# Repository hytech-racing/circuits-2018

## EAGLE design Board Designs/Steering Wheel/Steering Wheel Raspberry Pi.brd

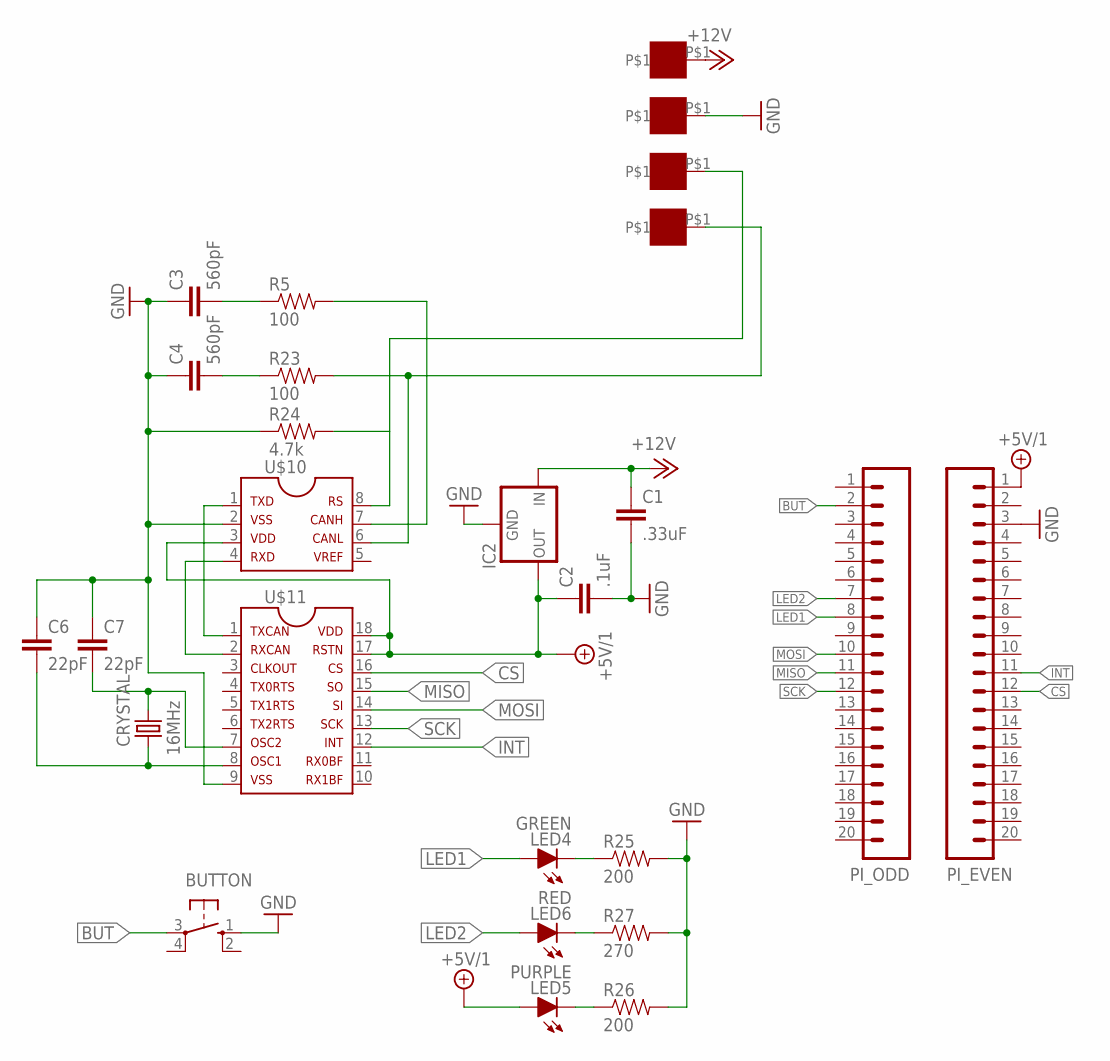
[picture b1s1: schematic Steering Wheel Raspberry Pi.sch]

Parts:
BUTTON: BTN_10-XX; B3F-10XX
C1: .33uF; 0805
C2: .1uF; 0805
C3, C4: 560pF; 0805
C6, C7: 22pF; 0805
CRYSTAL: 16MHz; HC49UP
IC2: OKI-78SR-5/1.5-W36-C_VERT; TO-220
LED4: GREEN; LED-805
LED5: PURPLE; LED-805
LED6: RED; LED-805
PI_EVEN: M20; 1X20
PI_ODD: M20; 1X20
R5, R23: 100; 0805
R24: 4.7k; 0805
R25, R26: 200; 0805
R27: 270; 0805
U$1, U$2, U$3, U$4: SOLDER_PAD; SOLDER_PAD_XSMALL
U$10: MCP2551; SOIC-08
U$11: MCP2515SMD; SOIC-18W

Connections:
+5V/1: C2.1, IC2.3 (OUT), LED5.A, PI_EVEN.1, U$10.3, U$11.17, U$11.18
+12V: C1.1, IC2.1 (IN), U$1.P$1
BUT: BUTTON.3, PI_ODD.2
CAN-H: R5.2, U$10.7
CAN-L: R23.2, U$4.P$1, U$10.6
CS: PI_EVEN.12, U$11.16
GND: BUTTON.1 (S), C1.2, C2.2, C3.1, C4.1, C6.1, C7.1, IC2.2 (GND), PI_EVEN.3, R24.1, R25.2, R26.2, R27.2, U$2.P$1, U$10.2, U$11.9
INT: PI_EVEN.11, U$11.12
LED1: LED4.A, PI_ODD.8
LED2: LED6.A, PI_ODD.7
MISO: PI_ODD.11, U$11.15
MOSI: PI_ODD.10, U$11.14
unnamed: U$10.1, U$11.1
unnamed: U$10.4, U$11.2
unnamed: C6.2, CRYSTAL.2, U$11.8
unnamed: R24.2, U$3.P$1, U$10.8
unnamed: C7.2, CRYSTAL.1, U$11.7
unnamed: C3.2, R5.1
unnamed: C4.2, R23.1
unnamed: LED4.C, R25.1
unnamed: LED5.C, R26.1
unnamed: LED6.C, R27.1
SCK: PI_ODD.12, U$11.13

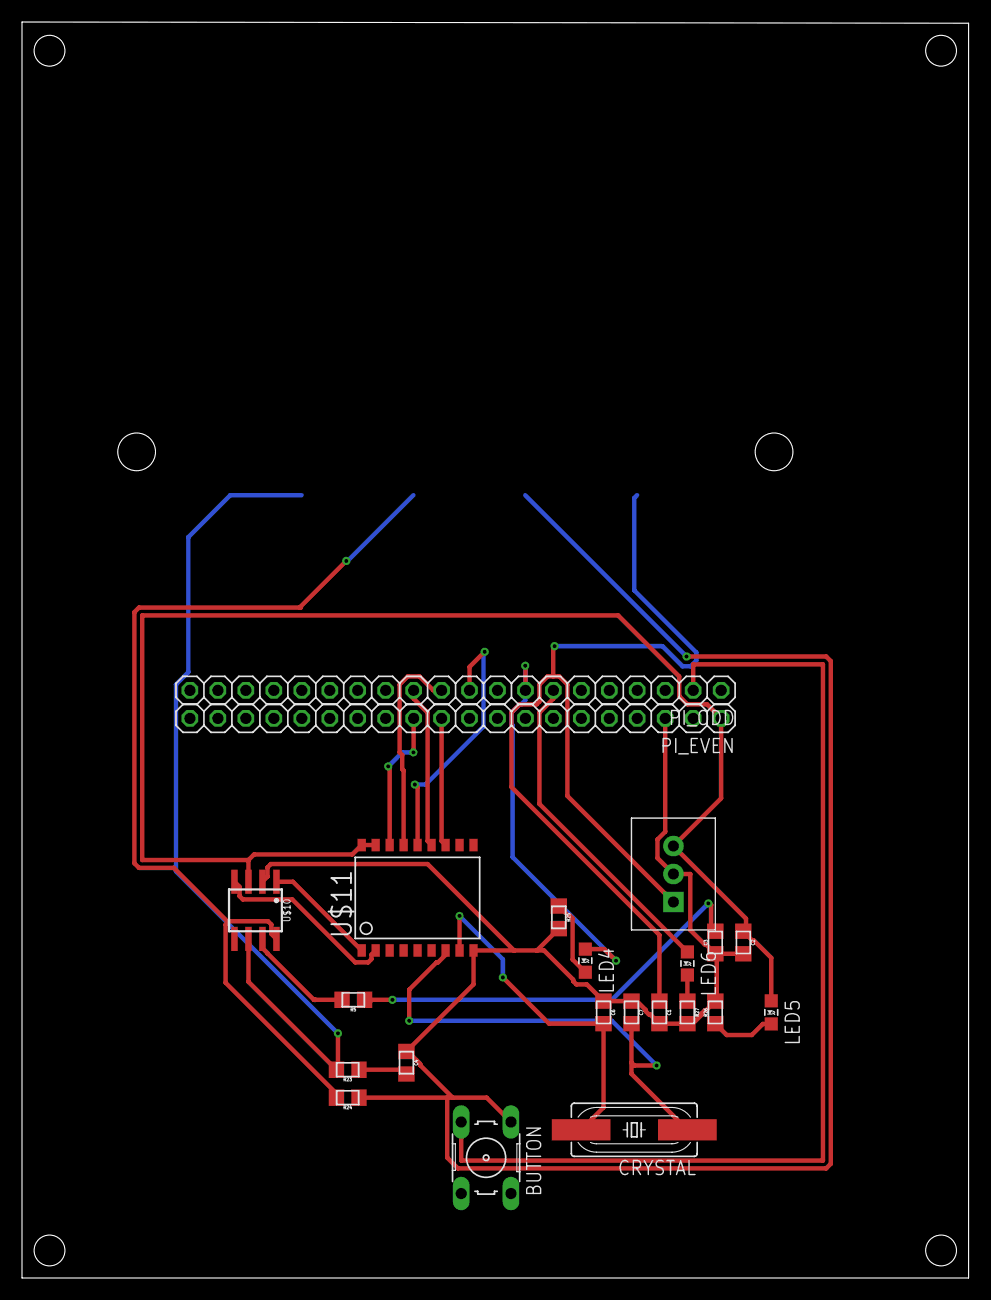
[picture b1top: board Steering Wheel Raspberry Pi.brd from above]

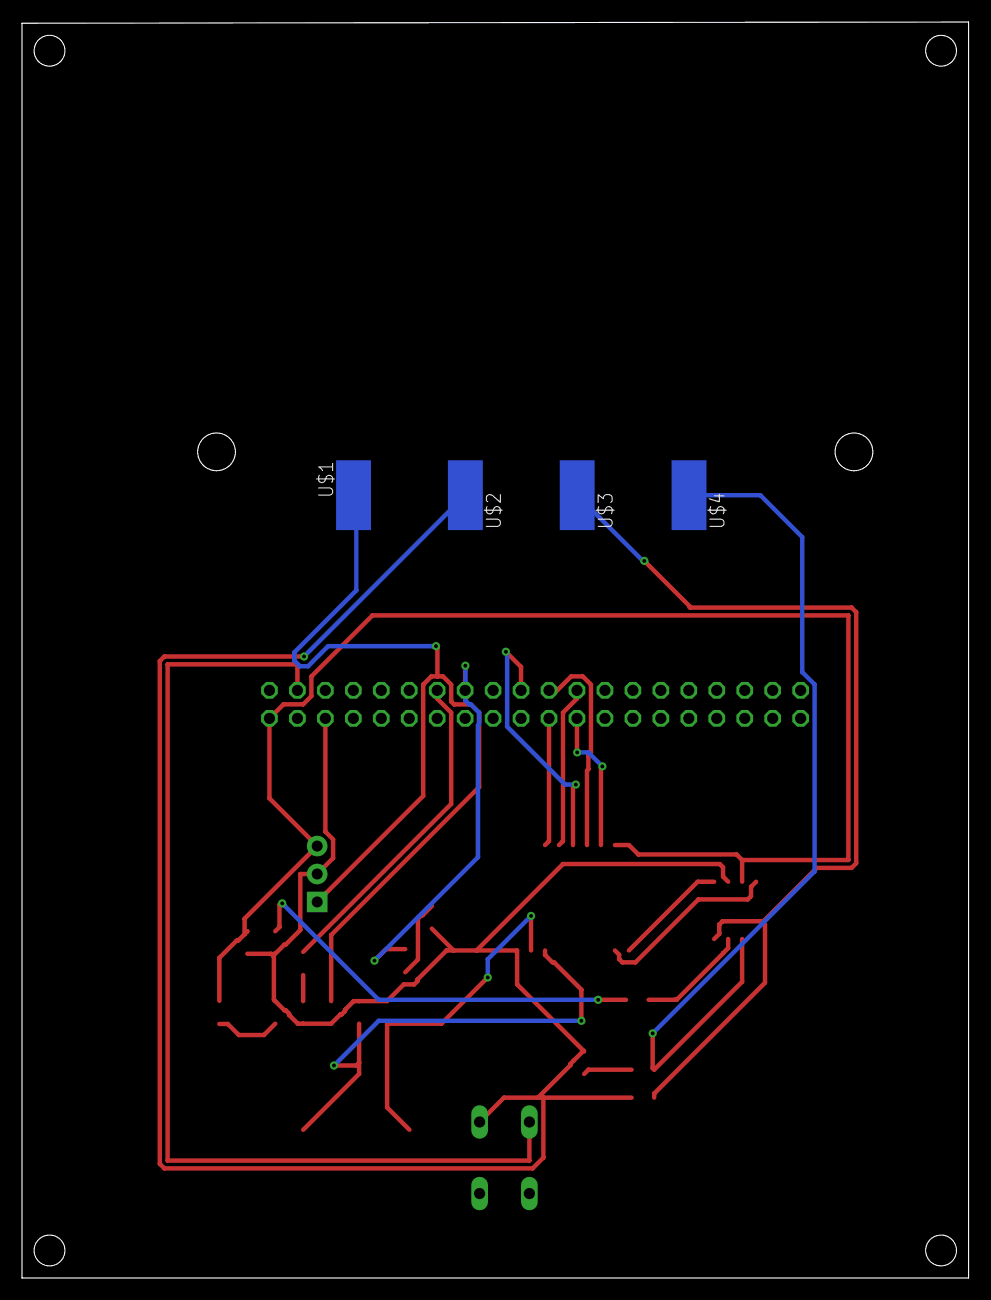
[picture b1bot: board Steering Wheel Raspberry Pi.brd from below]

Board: 2 copper layers, 86.0 x 114.1 mm, 26 parts (4 on the bottom side), 23 nets.

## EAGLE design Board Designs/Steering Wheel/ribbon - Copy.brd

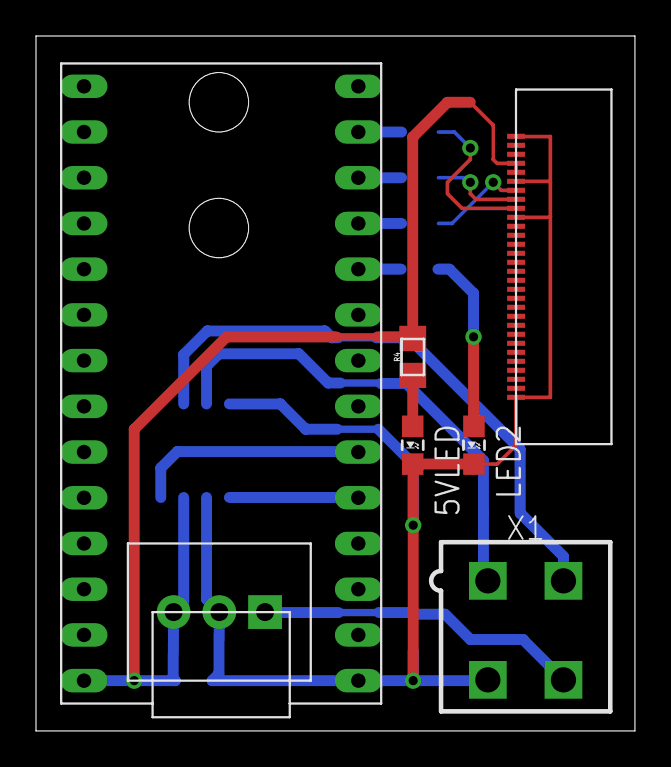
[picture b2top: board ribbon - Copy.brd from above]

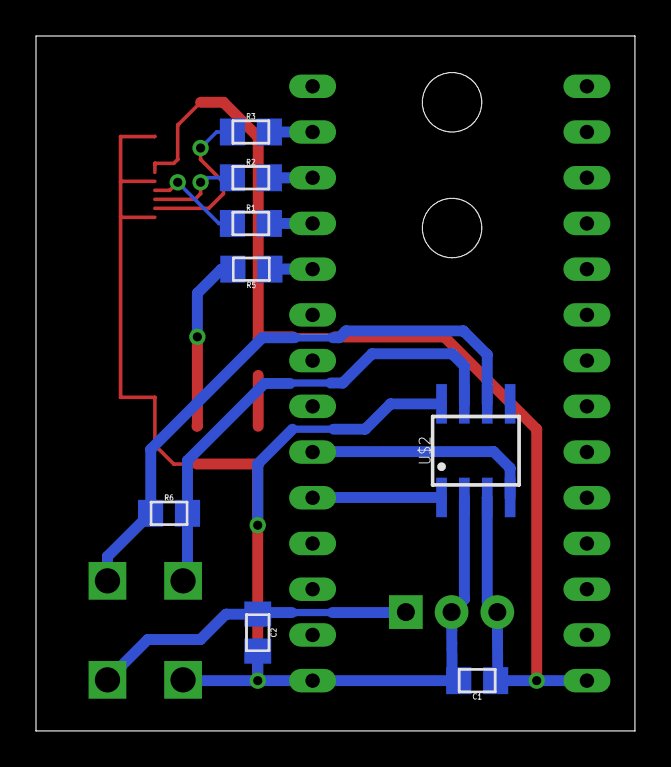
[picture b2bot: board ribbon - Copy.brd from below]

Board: 2 copper layers, 33.3 x 38.6 mm, 15 parts (8 on the bottom side), 16 nets.

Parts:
5VLED: LED-805
C1, C2: 0805
IC1: TO-220
LED2: LED-805
R1, R2, R3: 68; 0805
R4, R5: 450; 0805
R6: 120; 0805
U$1: TEENSY_3.2_SIMPLE
U$2: MCP2551; SOIC-08
U$3: FFC-30P-0.5MM
X1: CONNECTOR-4; MINIFIT_5566-4

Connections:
+5V: C1.1, IC1.3, R4.2, U$1.VIN, U$2.3, U$3.26, U$3.27
+12V: C2.1, IC1.1, X1.4
CANH: R6.2, U$2.7, X1.1
CANL: R6.1, U$2.6, X1.2
CANRX: U$1.D4(CANRX), U$2.4
CANTX: U$1.D3(CANTX), U$2.1
DISP_RX: R2.1, U$3.23
DISP_TX: R1.1, U$3.24
GND: 5VLED.C, C1.2, C2.2, IC1.2, LED2.C, U$1.GND, U$2.2, U$2.8, U$3.1, U$3.21, U$3.25, U$3.30, X1.3
unnamed: R1.2, U$1.D9(RX2)
unnamed: R2.2, U$1.D10(TX2)
unnamed: R3.2, U$1.D11
unnamed: 5VLED.A, R4.1
unnamed: LED2.A, R5.2
unnamed: R5.1, U$1.D8(TX3)
RESET: R3.1, U$3.22

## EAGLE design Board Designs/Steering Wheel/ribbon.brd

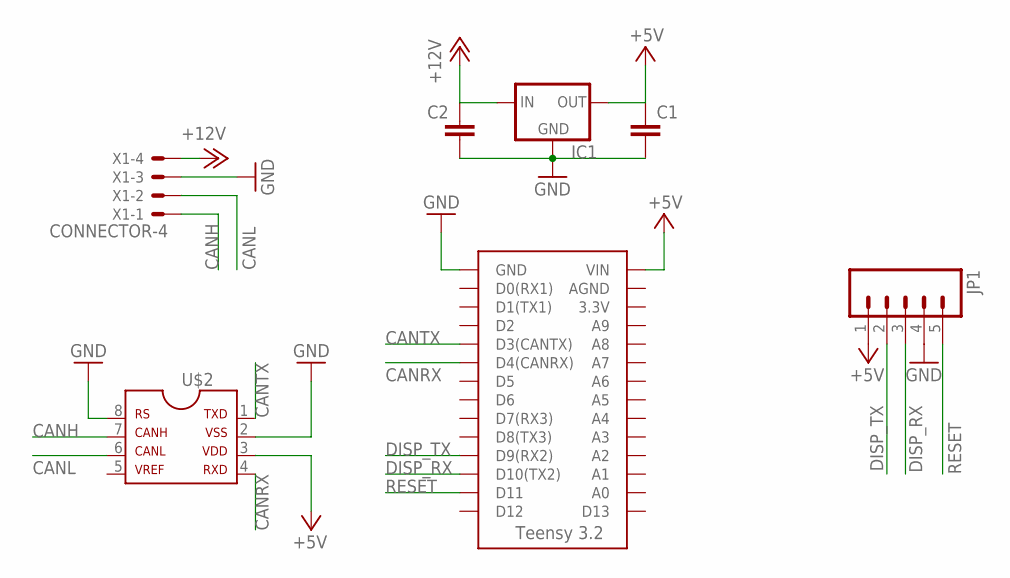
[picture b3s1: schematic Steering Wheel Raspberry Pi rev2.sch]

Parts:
C1, C2: CAP0805; 0805
IC1: 5VREG_L7805_VERT; TO-220
JP1: M05; 1X05
U$1: TEENSY_3.2_SIMPLE
U$2: MCP2551; SOIC-08
X1: CONNECTOR-4; MINIFIT_5566-4

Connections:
+5V: C1.1, IC1.3 (OUT), JP1.1, U$1.VIN, U$2.3
+12V: C2.1, IC1.1 (IN), X1.4
CANH: U$2.7, X1.1
CANL: U$2.6, X1.2
CANRX: U$1.D4(CANRX), U$2.4
CANTX: U$1.D3(CANTX), U$2.1
DISP_RX: JP1.3, U$1.D10(TX2)
DISP_TX: JP1.2, U$1.D9(RX2)
GND: C1.2, C2.2, IC1.2 (GND), JP1.4, U$1.GND, U$2.2, U$2.8, X1.3
RESET: JP1.5, U$1.D11

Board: 2 copper layers, 7 parts (0 on the bottom side), 10 nets, no tracks yet.

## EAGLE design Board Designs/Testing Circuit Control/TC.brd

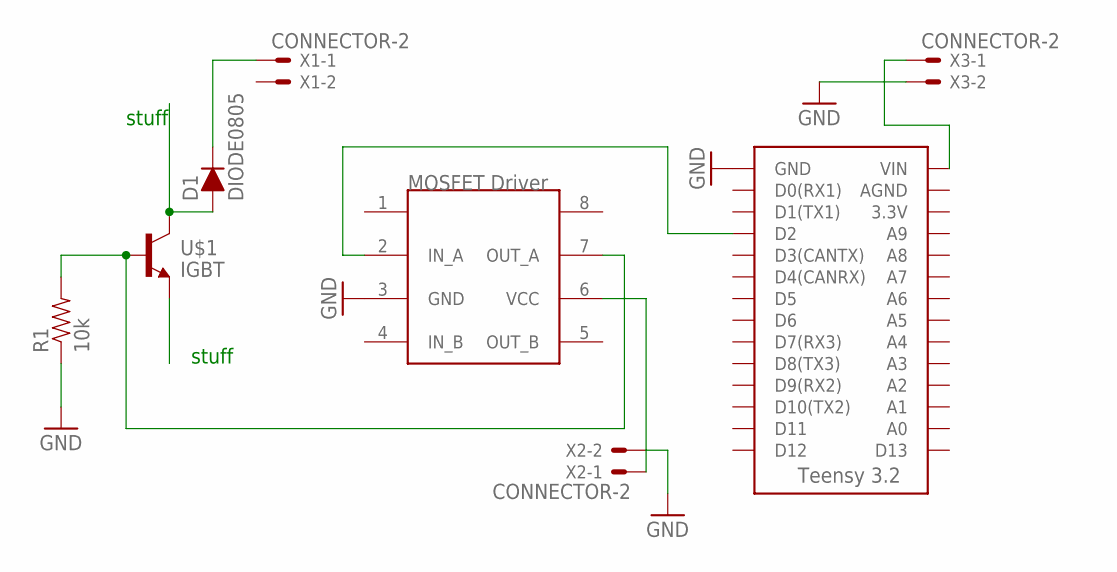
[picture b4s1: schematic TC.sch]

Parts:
D1: DIODE0805; 0805_D
R1: 10k; 0402-RES
U$1: IGBT
U$2: MC34152; SOIC-08
U$3: TEENSY_3.2_SIMPLE
X1, X2, X3: CONNECTOR-2; MINIFIT_5566-2

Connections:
GND: R1.1, U$2.3 (GND), U$3.GND, X2.2, X3.2
unnamed: D1.C, X1.1
unnamed: D1.A, U$1.P$2 (COLLECTOR)
unnamed: R1.2, U$1.P$3 (BASE), U$2.7 (OUT_A)
unnamed: U$2.2 (IN_A), U$3.D2
unnamed: U$1.P$1 (EMITTER), U$1.P$4 (EMITTER)
unnamed: U$2.6 (VCC), X2.1
unnamed: U$3.VIN, X3.1

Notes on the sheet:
stuff

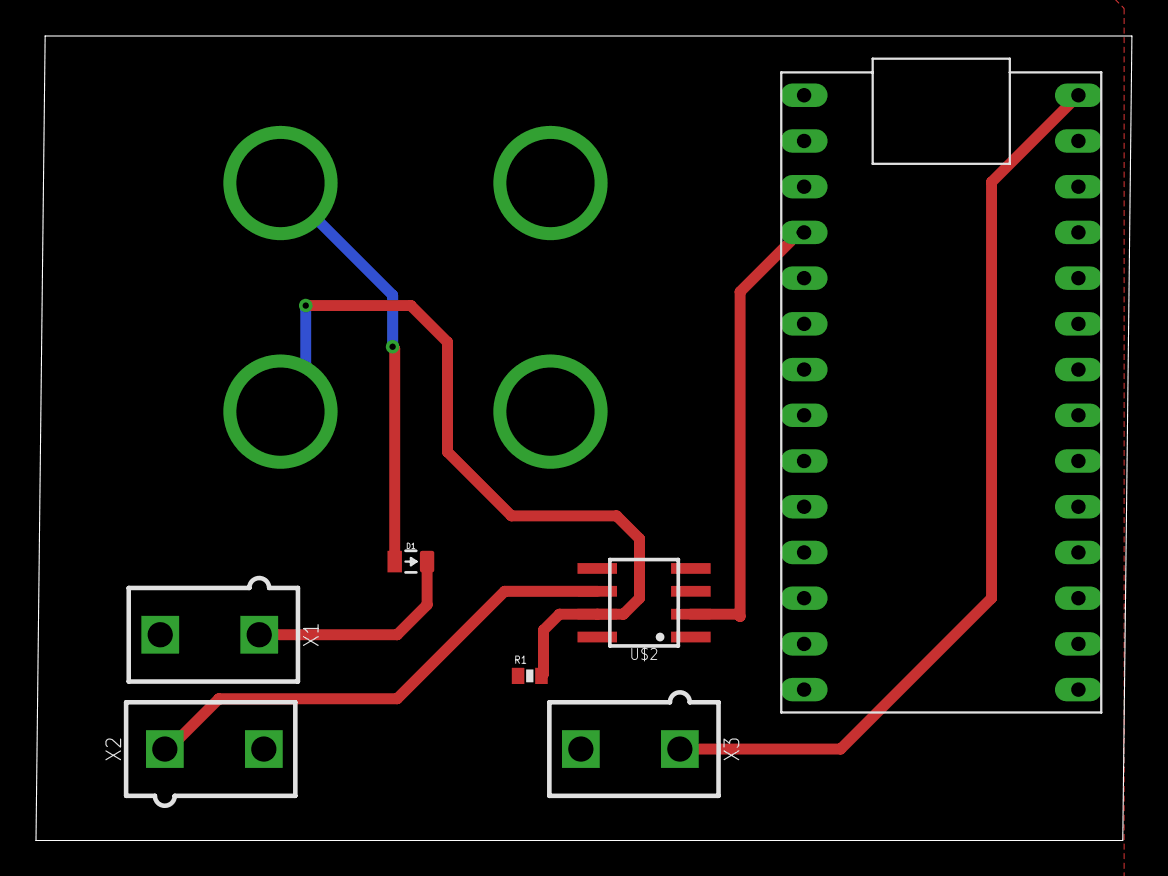
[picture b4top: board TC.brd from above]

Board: 2 copper layers, 60.9 x 44.7 mm, 8 parts (1 on the bottom side), 8 nets.

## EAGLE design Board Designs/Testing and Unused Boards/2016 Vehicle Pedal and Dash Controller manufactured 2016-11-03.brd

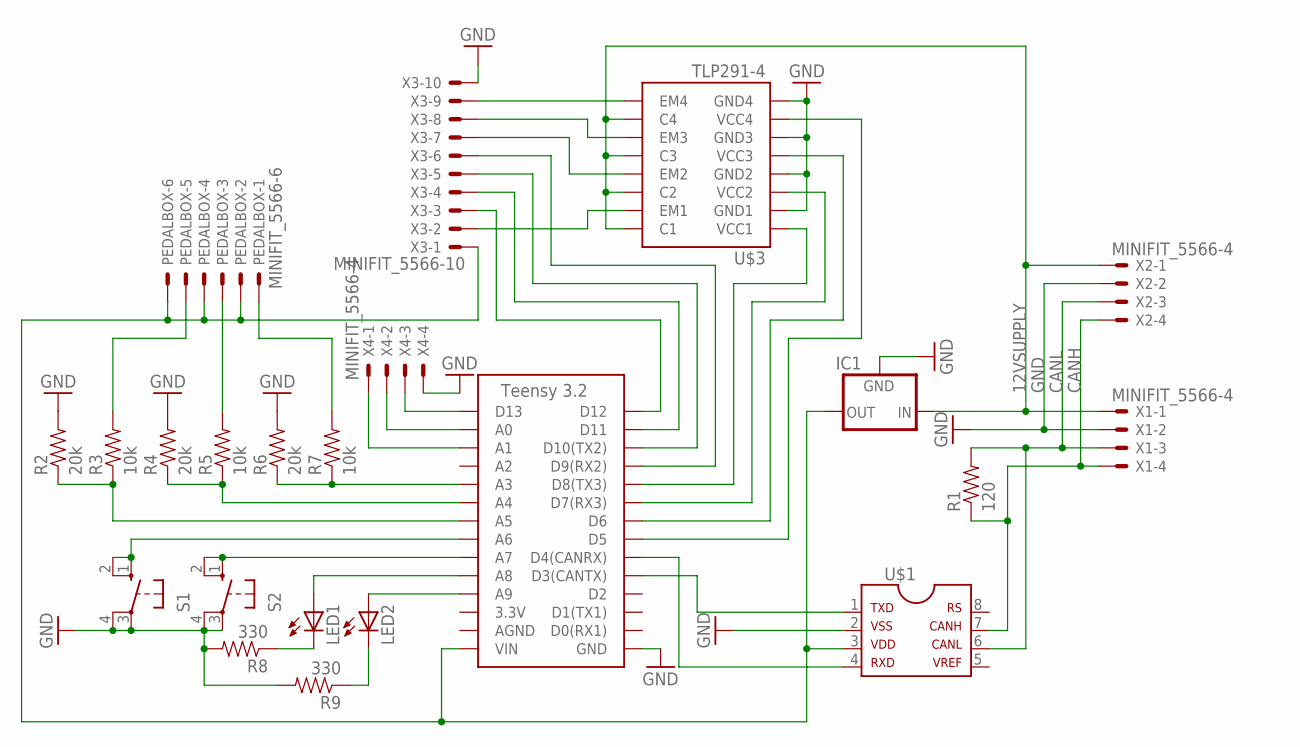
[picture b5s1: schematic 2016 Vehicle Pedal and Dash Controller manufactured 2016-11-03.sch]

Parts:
IC1: 5V_REGULATOR_LM340-NLM340MPX-5.0/NOPB; SOT223
LED1, LED2: LED-0805; LED-805
PEDALBOX: MINIFIT_5566-6
R1: 120; 0805
R2, R4, R6: 20k; 0805
R3, R5, R7: 10k; 0805
R8, R9: 330; 0805
S1, S2: BTN_10-XX; B3F-10XX
U$1: MCP2551; SOIC-08
U$2: TEENSY_3.2_SIMPLE
U$3: TLP291-4; SOIC-16
X1, X2, X4: MINIFIT_5566-4
X3: MINIFIT_5566-10

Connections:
12VSUPPLY: IC1.1 (IN), U$3.10 (C4), U$3.12 (C3), U$3.14 (C2), U$3.16 (C1), X1.1, X2.1
CANH: R1.1, U$1.7, X1.4, X2.4
CANL: R1.2, U$1.6, X1.3, X2.3
GND: IC1.2 (GND), IC1.4 (GND), R2.2, R4.2, R6.2, R8.2, R9.2, S1.3, S1.4 (P1), S2.3, S2.4 (P1), U$1.2, U$2.GND, U$3.2 (GND1), U$3.4 (GND2), U$3.6 (GND3), U$3.8 (GND4), X1.2, X2.2, X3.10, X4.4
unnamed: U$2.D12, X3.3
unnamed: IC1.3 (OUT), PEDALBOX.2, PEDALBOX.4, PEDALBOX.6, U$1.3, U$2.VIN, X3.1
unnamed: PEDALBOX.5, R3.2
unnamed: PEDALBOX.3, R5.2
unnamed: U$1.1, U$2.D3(CANTX)
unnamed: U$1.4, U$2.D4(CANRX)
unnamed: PEDALBOX.1, R7.2
unnamed: R2.1, R3.1, U$2.A5
unnamed: R4.1, R5.1, U$2.A4
unnamed: R6.1, R7.1, U$2.A3
unnamed: U$2.D11, X3.4
unnamed: U$2.D10(TX2), X3.5
unnamed: U$2.D9(RX2), X3.6
unnamed: U$2.D8(TX3), U$3.1 (VCC1)
unnamed: U$3.9 (EM4), X3.9
unnamed: U$3.11 (EM3), X3.8
unnamed: U$3.13 (EM2), X3.7
unnamed: U$3.15 (EM1), X3.2
unnamed: U$2.D7(RX3), U$3.3 (VCC2)
unnamed: U$2.D6, U$3.5 (VCC3)
unnamed: U$2.D5, U$3.7 (VCC4)
unnamed: S1.1 (S), S1.2 (S1), U$2.A6
unnamed: S2.1 (S), S2.2 (S1), U$2.A7
unnamed: LED1.A, U$2.A8
unnamed: LED2.A, U$2.A9
unnamed: LED1.C, R8.1
unnamed: LED2.C, R9.1
unnamed: U$2.D13, X4.3
unnamed: U$2.A0, X4.2
unnamed: U$2.A1, X4.1

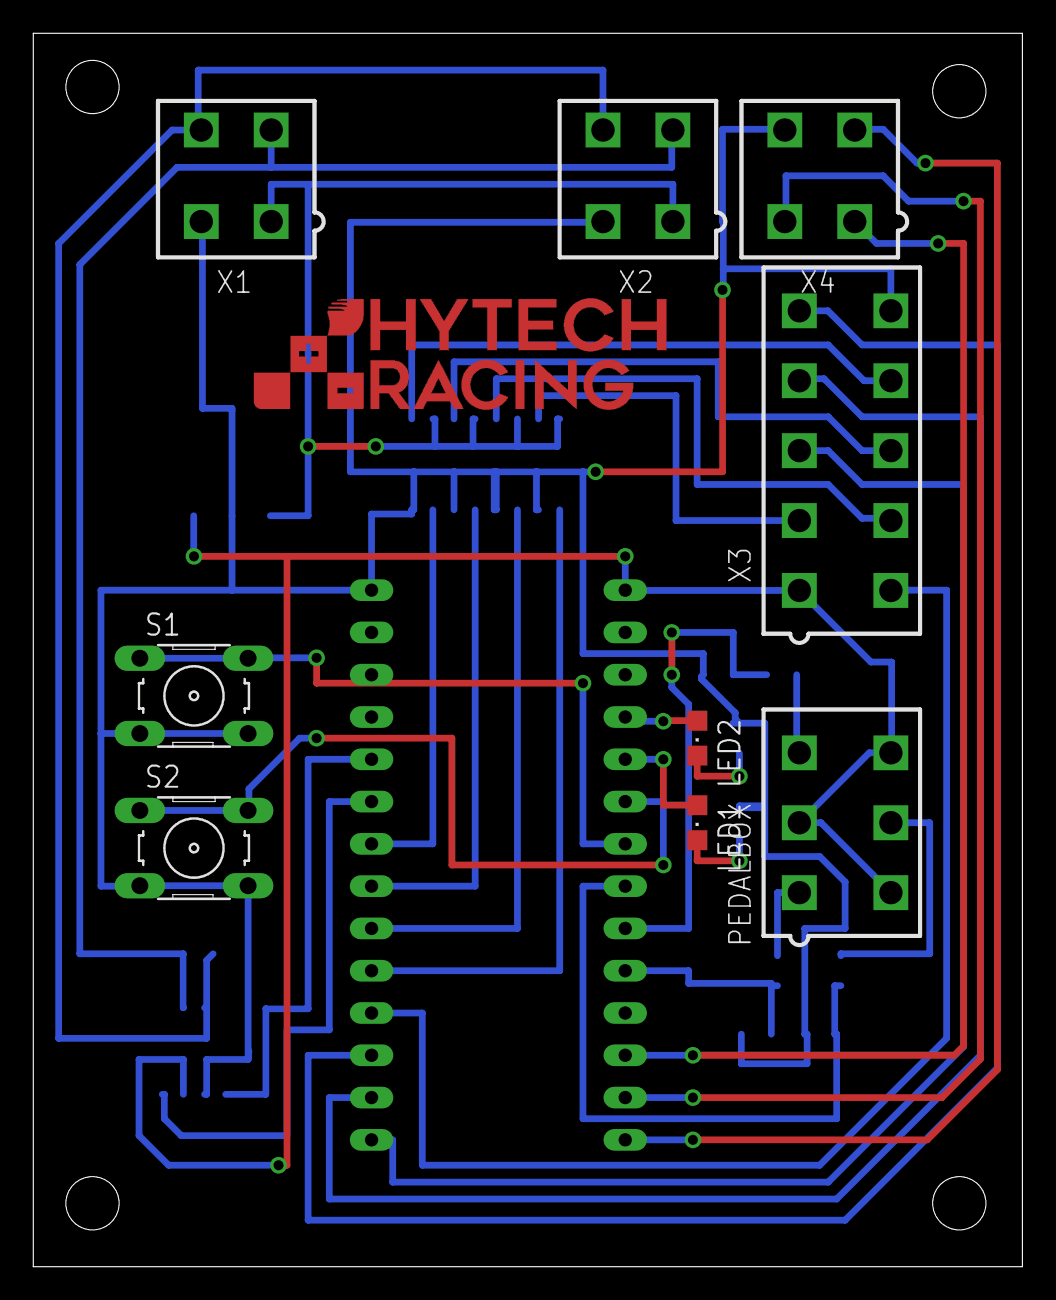
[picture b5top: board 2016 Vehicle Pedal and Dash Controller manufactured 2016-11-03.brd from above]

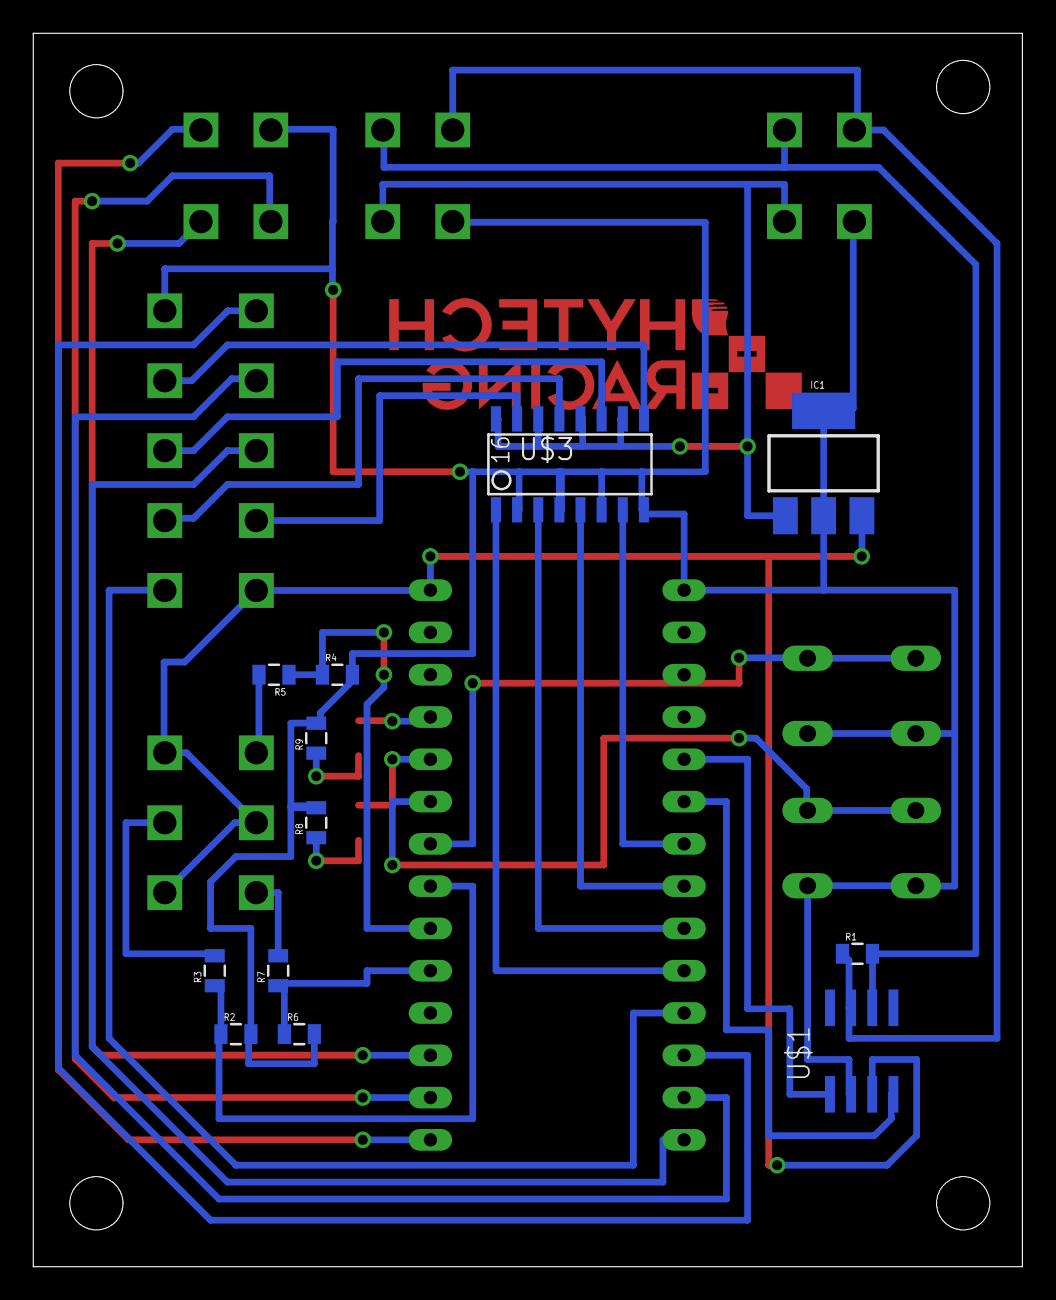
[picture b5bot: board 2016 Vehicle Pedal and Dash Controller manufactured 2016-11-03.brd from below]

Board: 2 copper layers, 59.4 x 74.1 mm, 22 parts (12 on the bottom side), 34 nets.

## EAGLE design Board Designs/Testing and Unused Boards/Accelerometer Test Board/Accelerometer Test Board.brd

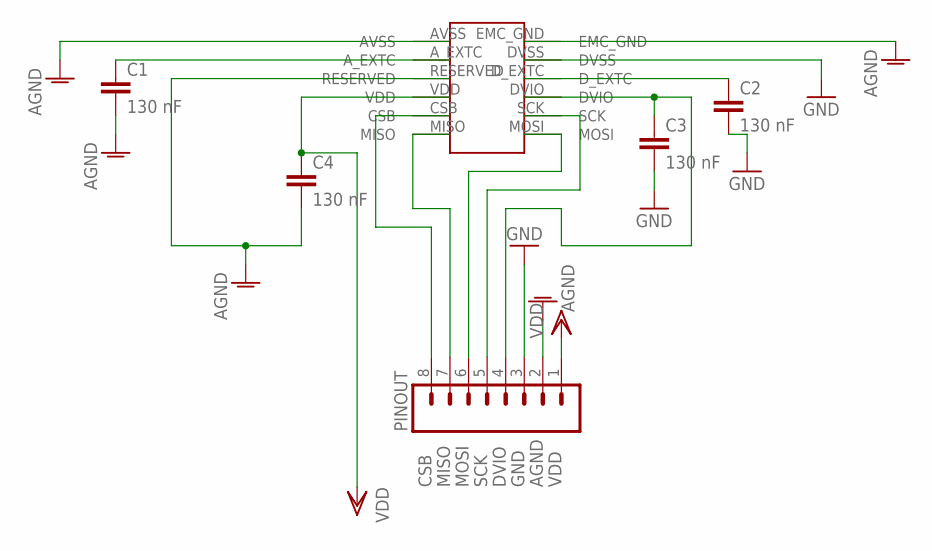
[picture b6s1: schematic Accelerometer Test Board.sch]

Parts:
C1, C2, C3, C4: 130 nF; 0805
PINOUT: M08; 1X08
U$1: SCA3100-D04

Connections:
AGND: C1.2, C4.2, PINOUT.2, U$1.AVSS, U$1.EMC_GND, U$1.RESERVED
CSB: PINOUT.8, U$1.CSB
DVIO: C3.1, PINOUT.4, U$1.DVIO
GND: C2.2, C3.2, PINOUT.3, U$1.DVSS
MISO: PINOUT.7, U$1.MISO
MOSI: PINOUT.6, U$1.MOSI
unnamed: C1.1, U$1.A_EXTC
unnamed: C2.1, U$1.D_EXTC
SCK: PINOUT.5, U$1.SCK
VDD: C4.1, PINOUT.1, U$1.VDD

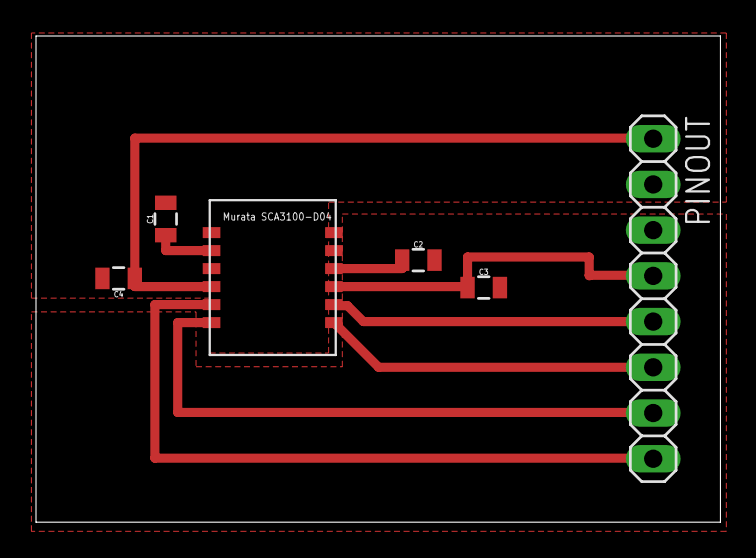
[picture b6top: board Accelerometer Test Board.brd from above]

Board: 2 copper layers, 38.0 x 27.0 mm, 6 parts (0 on the bottom side), 10 nets.

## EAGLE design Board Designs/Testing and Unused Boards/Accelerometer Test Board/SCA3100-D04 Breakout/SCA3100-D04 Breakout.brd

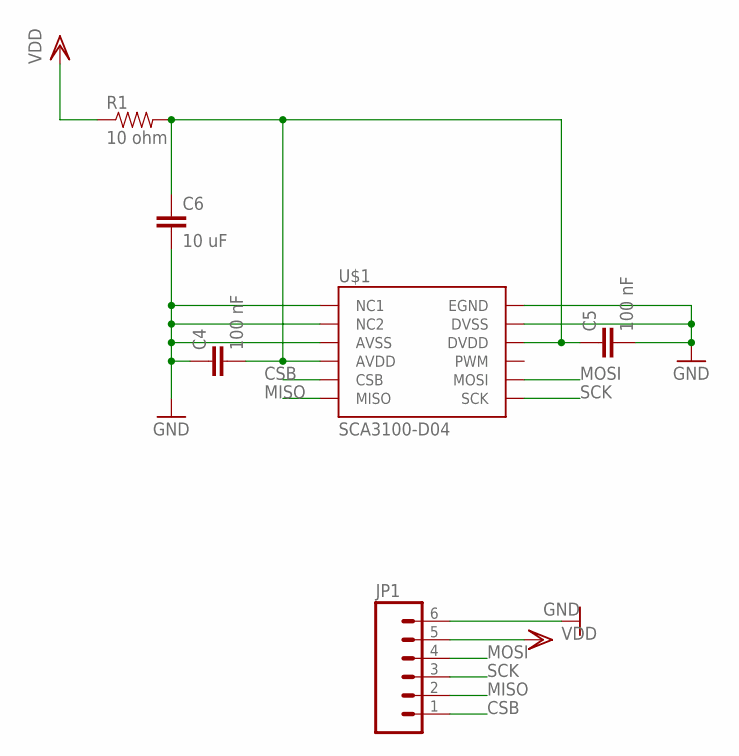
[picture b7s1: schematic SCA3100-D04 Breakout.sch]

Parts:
C4, C5: 100 nF; 0805
C6: 10 uF; 0805
JP1: M06; 1X06
R1: 10 ohm; 0805
U$1: SCA3100-D04

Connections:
CSB: JP1.1, U$1.CSB
GND: C4.1, C5.2, C6.2, JP1.6, U$1.AVSS, U$1.DVSS, U$1.EGND, U$1.NC1, U$1.NC2
MISO: JP1.2, U$1.MISO
MOSI: JP1.4, U$1.MOSI
unnamed: C4.2, C5.1, C6.1, R1.2, U$1.AVDD, U$1.DVDD
SCK: JP1.3, U$1.SCK
VDD: JP1.5, R1.1

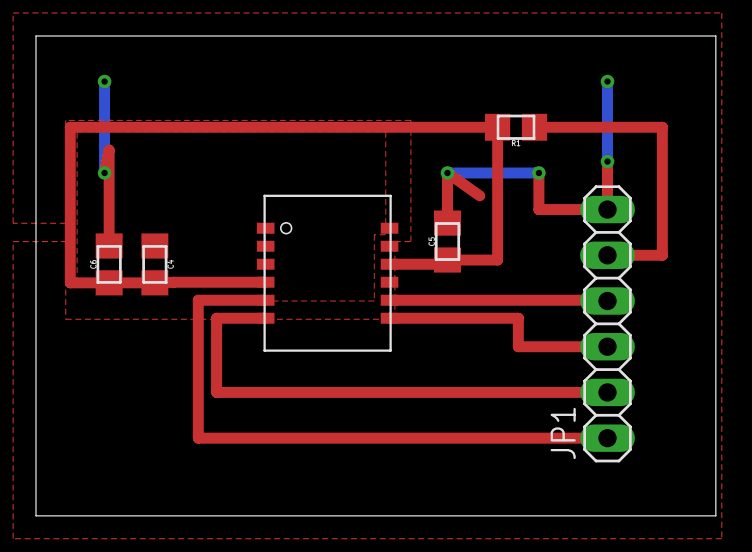
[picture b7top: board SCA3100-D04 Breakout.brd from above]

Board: 2 copper layers, 37.8 x 26.7 mm, 6 parts (0 on the bottom side), 7 nets.

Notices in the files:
parts and their libraries:
SparkFun-FreqCtrl: Licensing: Creative Commons ShareAlike 4.0 International - https://creativecommons.org/licenses/by-sa/4.0
